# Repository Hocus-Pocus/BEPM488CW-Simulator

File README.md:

# BEPM488CW-Simulator
Simulator hardware for the BEPM488CW project

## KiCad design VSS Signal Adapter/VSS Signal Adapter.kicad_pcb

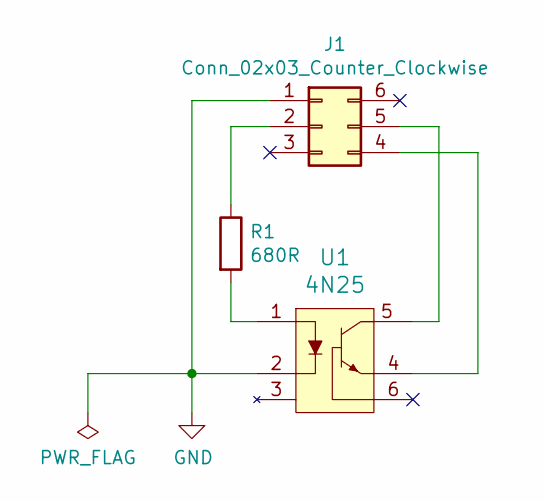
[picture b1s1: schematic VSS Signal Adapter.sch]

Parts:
J1: Conn_02x03_Counter_Clockwise; DIP-6_W7.62mm
R1: 680R; R_Axial_DIN0207_L6.3mm_D2.5mm_P10.16mm_Horizontal
U1: 4N25; DIP-6_W7.62mm; MPN 4N25; Digi-Key_PN 160-1300-5-ND

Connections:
GND: J1.1, U1.2
unnamed: J1.2, R1.1
unnamed: J1.4, U1.4
unnamed: J1.5, U1.5
unnamed: R1.2, U1.1

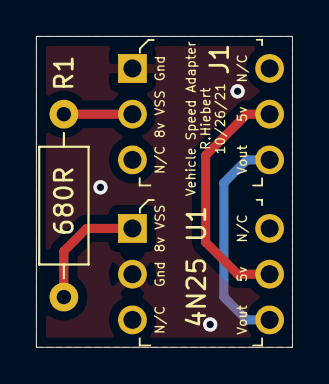
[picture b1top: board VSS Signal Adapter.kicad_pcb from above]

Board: 2 copper layers, 14.2 x 17.3 mm, 3 parts (0 on the bottom side), 5 nets.

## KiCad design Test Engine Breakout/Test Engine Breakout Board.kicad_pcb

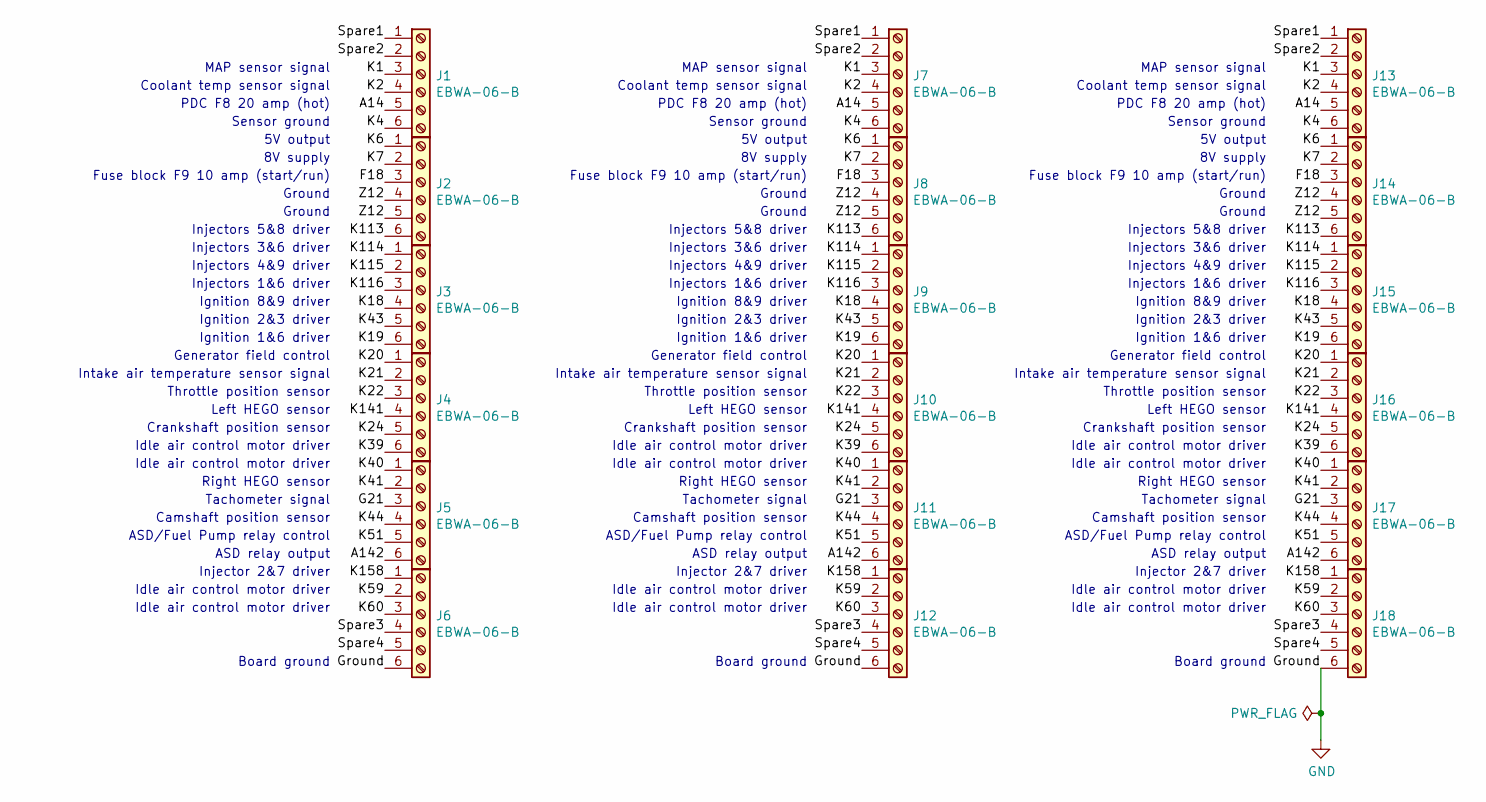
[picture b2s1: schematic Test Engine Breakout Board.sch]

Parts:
J1, J2, J3, J4, J5, J6, J7, J8, J9, J10, J11, J12, J13, J14, J15, J16, J17, J18: EBWA-06-B

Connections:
/A14: J1.5, J7.5, J13.5
/A142: J5.6, J11.6, J17.6
/F18: J2.3, J8.3, J14.3
/G21: J5.3, J11.3, J17.3
/K1: J1.3, J7.3, J13.3
/K2: J1.4, J7.4, J13.4
/K4: J1.6, J7.6, J13.6
/K6: J2.1, J8.1, J14.1
/K7: J2.2, J8.2, J14.2
/K18: J3.4, J9.4, J15.4
/K19: J3.6, J9.6, J15.6
/K20: J4.1, J10.1, J16.1
/K21: J4.2, J10.2, J16.2
/K22: J4.3, J10.3, J16.3
/K24: J4.5, J10.5, J16.5
/K39: J4.6, J10.6, J16.6
/K40: J5.1, J11.1, J17.1
/K41: J5.2, J11.2, J17.2
/K43: J3.5, J9.5, J15.5
/K44: J5.4, J11.4, J17.4
/K51: J5.5, J11.5, J17.5
/K59: J6.2, J12.2, J18.2
/K60: J6.3, J12.3, J18.3
/K113: J2.6, J8.6, J14.6
/K114: J3.1, J9.1, J15.1
/K115: J3.2, J9.2, J15.2
/K116: J3.3, J9.3, J15.3
/K141: J4.4, J10.4, J16.4
/K158: J6.1, J12.1, J18.1
/Spare1: J1.1, J7.1, J13.1
/Spare2: J1.2, J7.2, J13.2
/Spare3: J6.4, J12.4, J18.4
/Spare4: J6.5, J12.5, J18.5
/Z12: J2.4, J2.5, J8.4, J8.5, J14.4, J14.5
GND: J6.6, J12.6, J18.6

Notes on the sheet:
MAP sensor signal
Coolant temp sensor signal
PDC F8 20 amp (hot)
Sensor ground
5V output
8V supply
Fuse block F9 10 amp (start/run)
Ground
Injectors 5&8 driver
Injectors 3&6 driver
Injectors 4&9 driver
Injectors 1&6 driver
Ignition 8&9 driver
Ignition 2&3 driver
Ignition 1&6 driver
Generator field control
Intake air temperature sensor signal
Throttle position sensor
Left HEGO sensor
Crankshaft position sensor
Idle air control motor driver
Right HEGO sensor
Tachometer signal
Camshaft position sensor
ASD/Fuel Pump relay control
ASD relay output
Injector 2&7 driver
Board ground

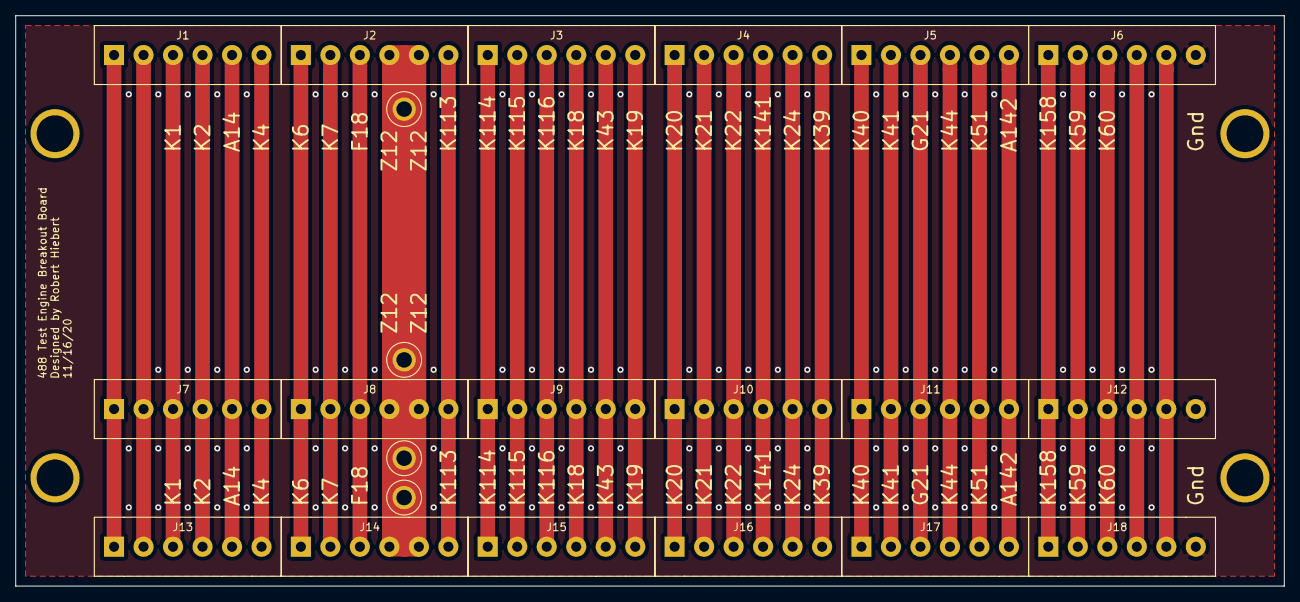
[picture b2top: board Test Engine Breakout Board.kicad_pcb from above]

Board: 2 copper layers, 163.8 x 73.7 mm, 18 parts (0 on the bottom side), 35 nets.

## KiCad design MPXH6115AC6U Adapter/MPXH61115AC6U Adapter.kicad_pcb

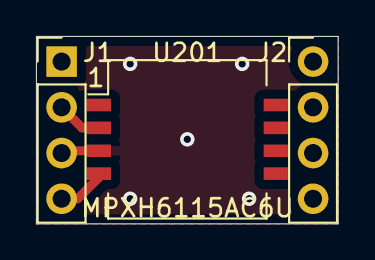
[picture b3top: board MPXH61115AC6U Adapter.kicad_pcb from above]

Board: 2 copper layers, 16.8 x 10.4 mm, 3 parts (0 on the bottom side), 3 nets.

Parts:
J1: Conn_01x04-1to4; PinHeader_1x04_P2.54mm_Vertical_1to4
J2: Conn_01x04_5to8; PinHeader_1x04_P2.54mm_Vertical_5to8
U201: MPXH6115AC6U; Freescale_98ARH99089A

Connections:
+5V: J1.2, U201.2
GND: J1.3, U201.3
unnamed: J1.4, U201.4

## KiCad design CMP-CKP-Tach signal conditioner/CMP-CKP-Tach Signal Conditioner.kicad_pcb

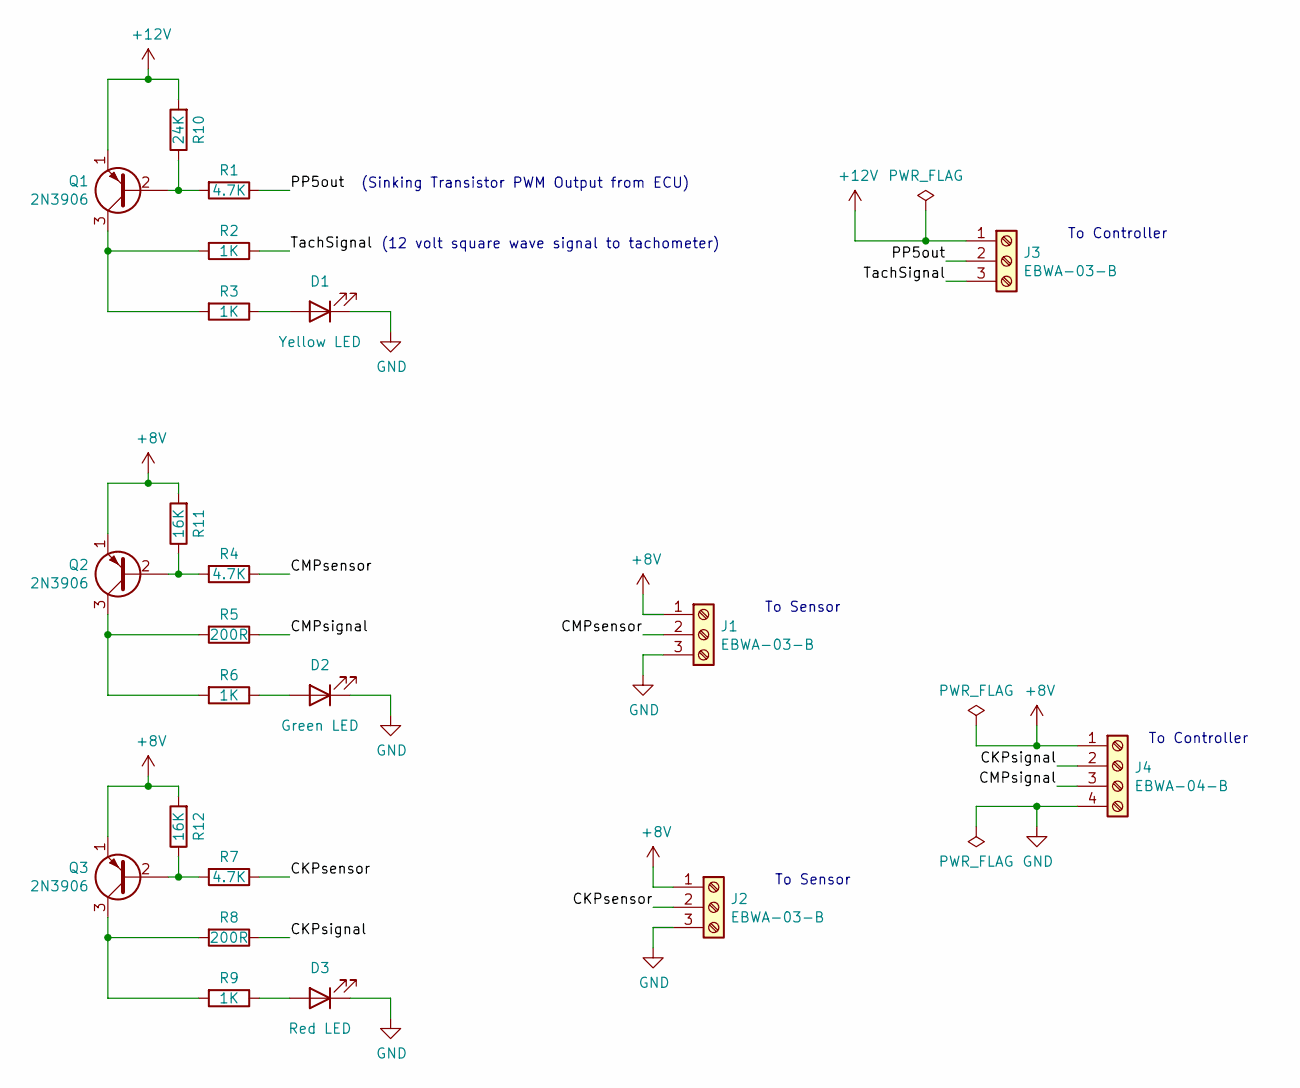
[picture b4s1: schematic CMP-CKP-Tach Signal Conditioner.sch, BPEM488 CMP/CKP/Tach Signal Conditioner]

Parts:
D1: Yellow LED; LED_D3.0mm; Digikey PN VA0L-3MDE2-ND
D2: Green LED; LED_D3.0mm; Digikey PN VA0L-3MDE2-ND
D3: Red LED; LED_D3.0mm
J1: EBWA-03-B; Digikey PN 2057-EBWA-03-B-ND
J2, J3: EBWA-03-B
J4: EBWA-04-B; Digikey PN 2057-EBWA-04-B-ND
Q1, Q2, Q3: 2N3906; TO-92_Wide
R1, R4, R7: 4.7K; R_Axial_DIN0207_L6.3mm_D2.5mm_P7.62mm_Horizontal
R2, R3, R6, R9: 1K; R_Axial_DIN0207_L6.3mm_D2.5mm_P7.62mm_Horizontal
R5, R8: 200R; R_Axial_DIN0207_L6.3mm_D2.5mm_P7.62mm_Horizontal
R10: 24K; R_Axial_DIN0207_L6.3mm_D2.5mm_P7.62mm_Horizontal
R11, R12: 16K; R_Axial_DIN0207_L6.3mm_D2.5mm_P7.62mm_Horizontal

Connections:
+8V: J1.1, J2.1, J4.1, Q2.1 (E), Q3.1 (E), R11.2, R12.2
+12V: J3.1, Q1.1 (E), R10.2
/CKPsensor: J2.2, R7.1
/CKPsignal: J4.2, R8.1
/CMPsensor: J1.2, R4.1
/CMPsignal: J4.3, R5.1
/PP5out: J3.2, R1.1
/TachSignal: J3.3, R2.1
GND: D1.1 (K), D2.1 (K), D3.1 (K), J1.3, J2.3, J4.4
unnamed: D1.2 (A), R3.1
unnamed: D2.2 (A), R6.1
unnamed: D3.2 (A), R9.1
unnamed: Q1.2 (B), R1.2, R10.1
unnamed: Q1.3 (C), R2.2, R3.2
unnamed: Q2.2 (B), R4.2, R11.1
unnamed: Q2.3 (C), R5.2, R6.2
unnamed: Q3.2 (B), R7.2, R12.1
unnamed: Q3.3 (C), R8.2, R9.2

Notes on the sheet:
(Sinking Transistor PWM Output from ECU)
(12 volt square wave signal to tachometer)
To Sensor
To Controller

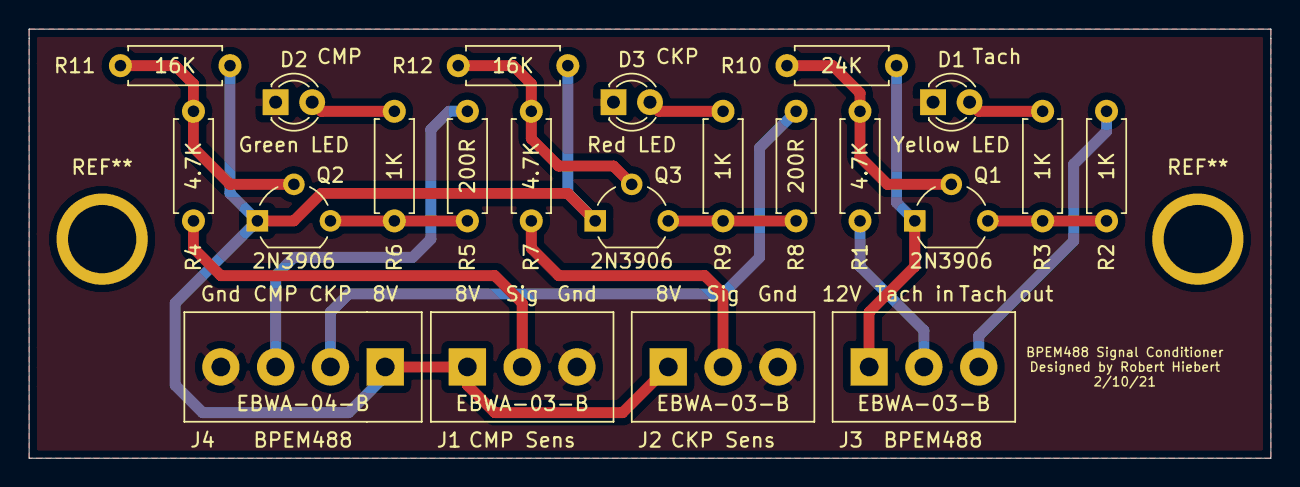
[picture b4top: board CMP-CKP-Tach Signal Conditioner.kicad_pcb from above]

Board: 2 copper layers, 86.4 x 29.8 mm, 22 parts (0 on the bottom side), 18 nets.

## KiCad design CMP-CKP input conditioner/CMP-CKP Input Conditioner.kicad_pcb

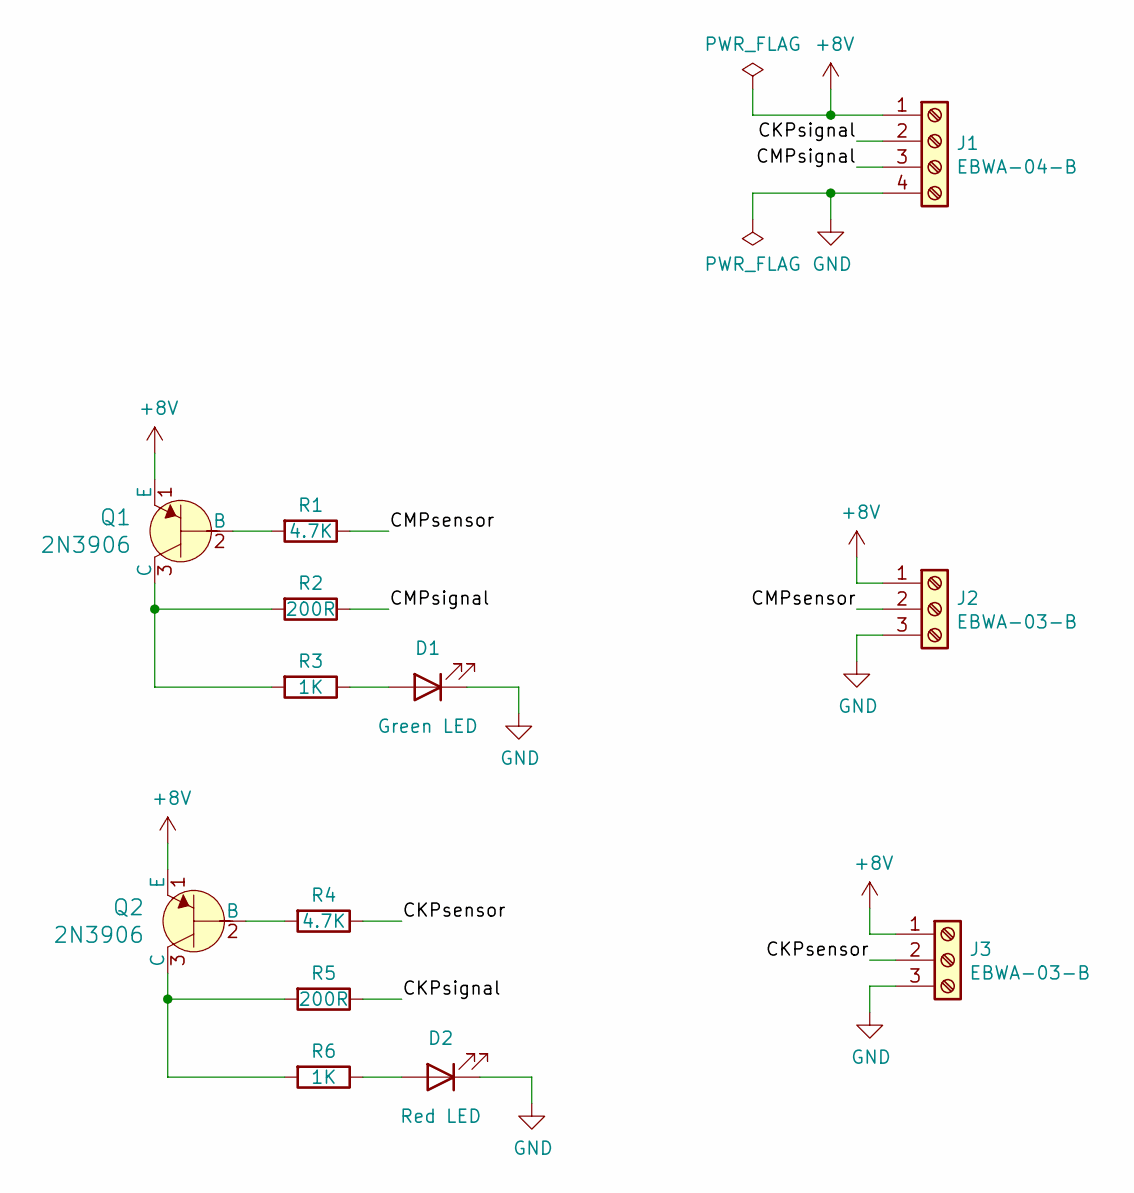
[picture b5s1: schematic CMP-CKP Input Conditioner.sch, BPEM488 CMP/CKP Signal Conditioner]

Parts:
D1: Green LED; LED_D3.0mm; Digikey PN VA0L-3MDE2-ND
D2: Red LED; LED_D3.0mm
J1: EBWA-04-B; Digikey PN 2057-EBWA-04-B-ND
J2: EBWA-03-B; Digikey PN 2057-EBWA-03-B-ND
J3: EBWA-03-B
Q1, Q2: 2N3906; TO-92_Wide; MPN 2N3906; Digi-Key_PN 2N3906APCT-ND
R1, R4: 4.7K; R_Axial_DIN0207_L6.3mm_D2.5mm_P7.62mm_Horizontal
R2, R5: 200R; R_Axial_DIN0207_L6.3mm_D2.5mm_P7.62mm_Horizontal
R3, R6: 1K; R_Axial_DIN0207_L6.3mm_D2.5mm_P7.62mm_Horizontal

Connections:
+8V: J1.1, J2.1, J3.1, Q1.1 (E), Q2.1 (E)
/CKPsensor: J3.2, R4.1
/CKPsignal: J1.2, R5.1
/CMPsensor: J2.2, R1.1
/CMPsignal: J1.3, R2.1
GND: D1.1 (K), D2.1 (K), J1.4, J2.3, J3.3
unnamed: D1.2 (A), R3.1
unnamed: D2.2 (A), R6.1
unnamed: Q1.2 (B), R1.2
unnamed: Q1.3 (C), R2.2, R3.2
unnamed: Q2.2 (B), R4.2
unnamed: Q2.3 (C), R5.2, R6.2

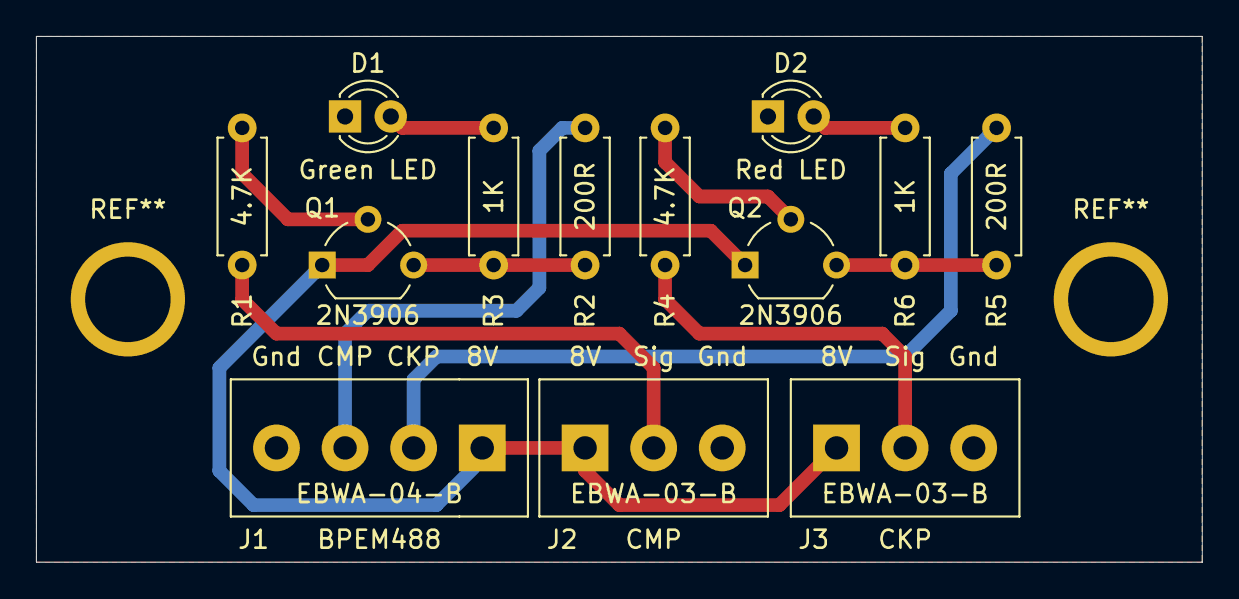
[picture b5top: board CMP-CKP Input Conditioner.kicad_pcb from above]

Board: 2 copper layers, 64.8 x 29.2 mm, 13 parts (0 on the bottom side), 12 nets.

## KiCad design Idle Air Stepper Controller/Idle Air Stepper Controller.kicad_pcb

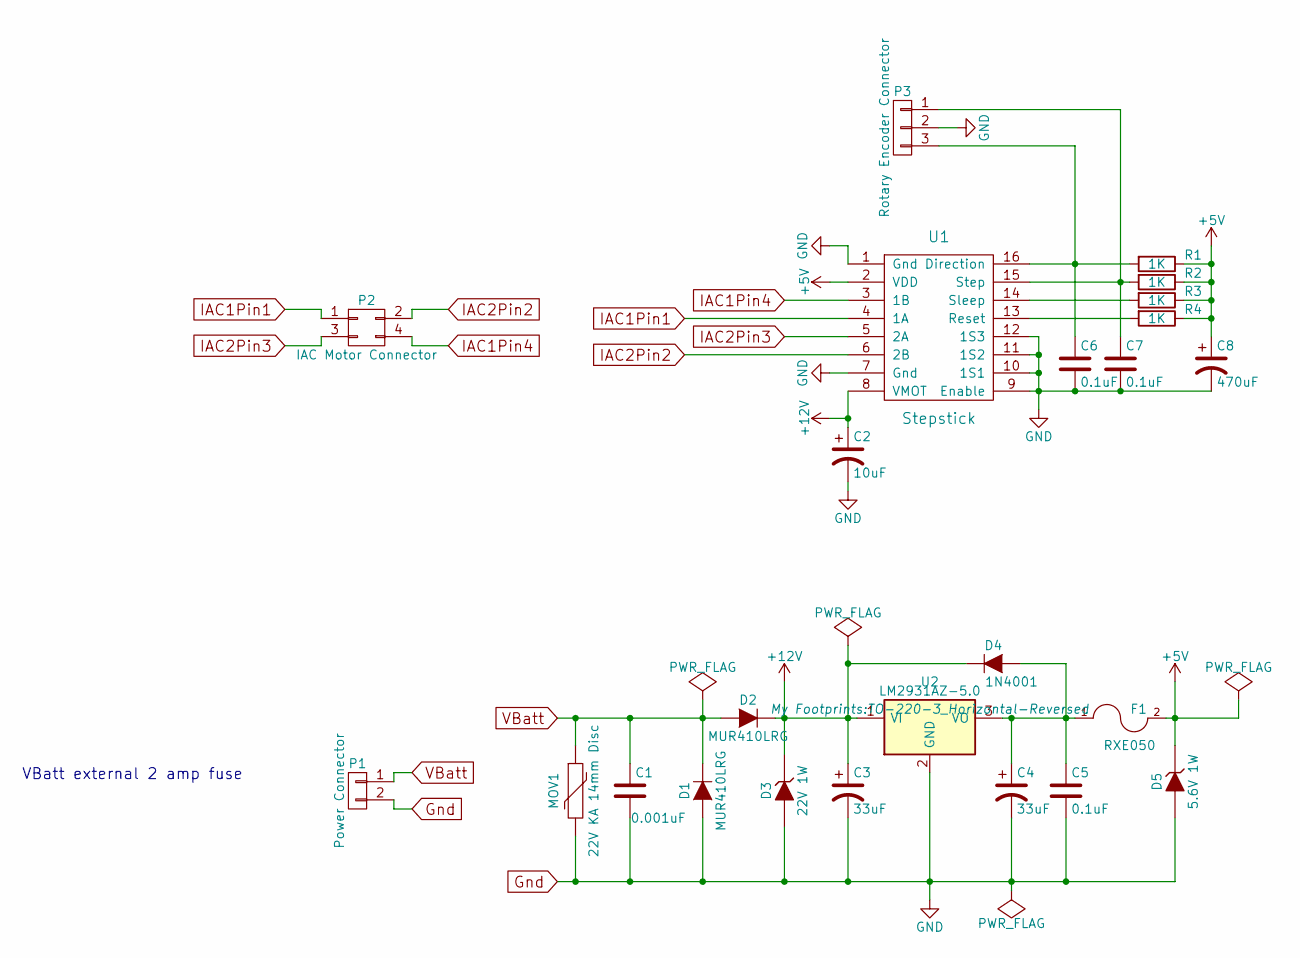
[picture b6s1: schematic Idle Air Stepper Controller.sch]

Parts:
C1: 0.001uF; 1000pF
C2: 10uF
C3, C4: 33uF
C5, C6, C7: 0.1uF
C8: 470uF
D1, D2: MUR410LRG; MUR410RLG
D3: 22V 1W; SmallZener
D4: 1N4001; 1N4001G
D5: 5.6V 1W; SmallZener
F1: RXE050; RXEF050
MOV1: 22V KA 14mm Disc; 14mmVar
P1: Power Connector; Molex-Microfit3-Single2-90
P2: IAC Motor Connector; Molex-Microfit3-Dual4-90
P3: Rotary Encoder Connector; Molex-Microfit3-Single3-90
R1, R2, R3, R4: 1K; .25Wresistor
U1: Stepstick
U2: LM2931AZ-5.0; TO-220-3_Horizontal-Reversed

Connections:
+5V: C8.1, D5.1 (K), F1.2, R1.1, R2.1, R3.1, R4.1, U1.2 (VDD)
+12V: C2.1, C3.1, D2.1 (K), D3.1 (K), D4.1 (K), U1.8 (VMOT), U2.1 (VI)
Gnd: C1.2, C2.2, C3.2, C4.2, C5.2, C6.2, C7.2, C8.2, D1.2 (A), D3.2 (A), D5.2 (A), MOV1.2, P1.2, P3.2, U1.1 (Gnd), U1.7 (Gnd), U1.9 (Enable), U1.10 (1S1), U1.11 (1S2), U1.12 (1S3), U2.2 (GND)
IAC1Pin1: P2.1, U1.4 (1A)
IAC1Pin4: P2.4, U1.3 (1B)
IAC2Pin2: P2.2, U1.6 (2B)
IAC2Pin3: P2.3, U1.5 (2A)
unnamed: C4.1, C5.1, D4.2 (A), F1.1, U2.3 (VO)
unnamed: C6.1, P3.3, R1.2, U1.16 (Direction)
unnamed: C7.1, P3.1, R2.2, U1.15 (Step)
unnamed: R3.2, U1.14 (Sleep)
unnamed: R4.2, U1.13 (Reset)
VBatt: C1.1, D1.1 (K), D2.2 (A), MOV1.1, P1.1

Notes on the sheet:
VBatt external 2 amp fuse

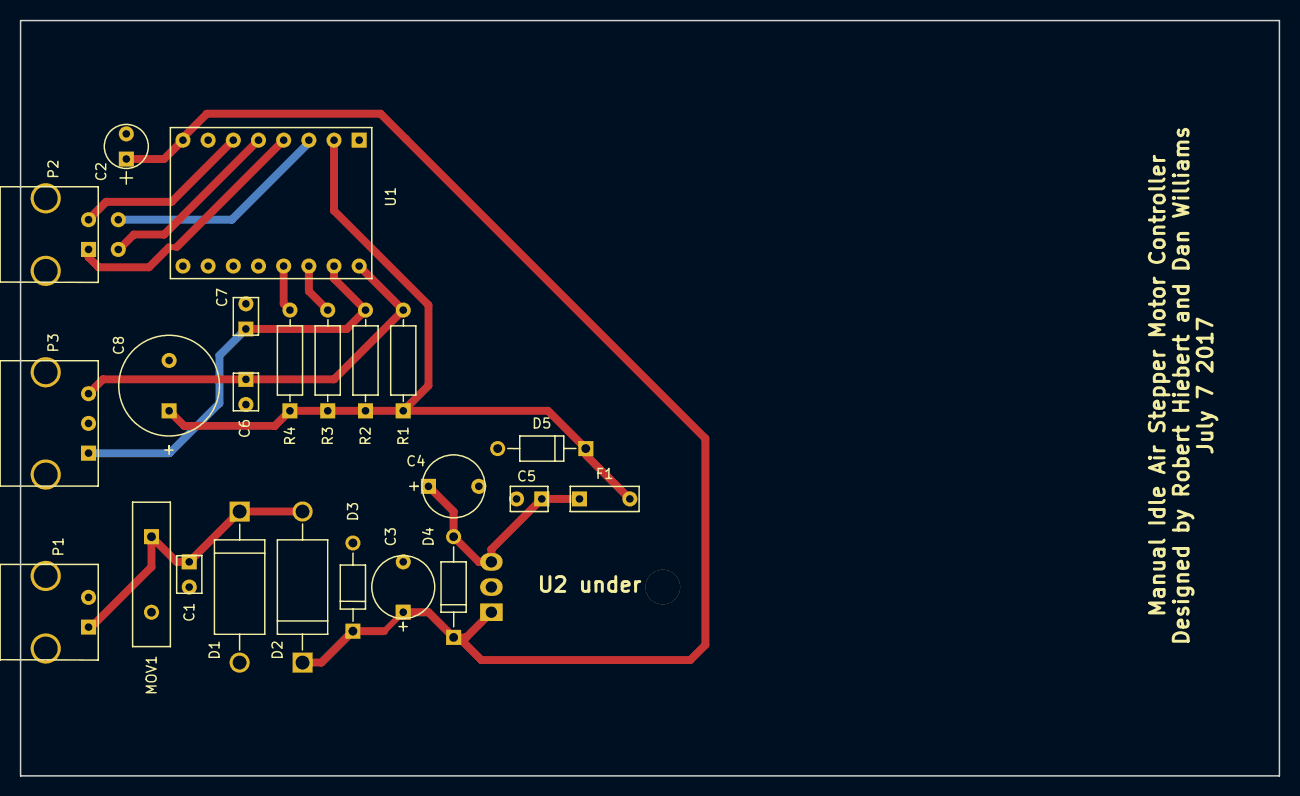
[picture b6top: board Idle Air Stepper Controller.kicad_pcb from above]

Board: 2 copper layers, 127.0 x 76.2 mm, 24 parts (1 on the bottom side), 13 nets.

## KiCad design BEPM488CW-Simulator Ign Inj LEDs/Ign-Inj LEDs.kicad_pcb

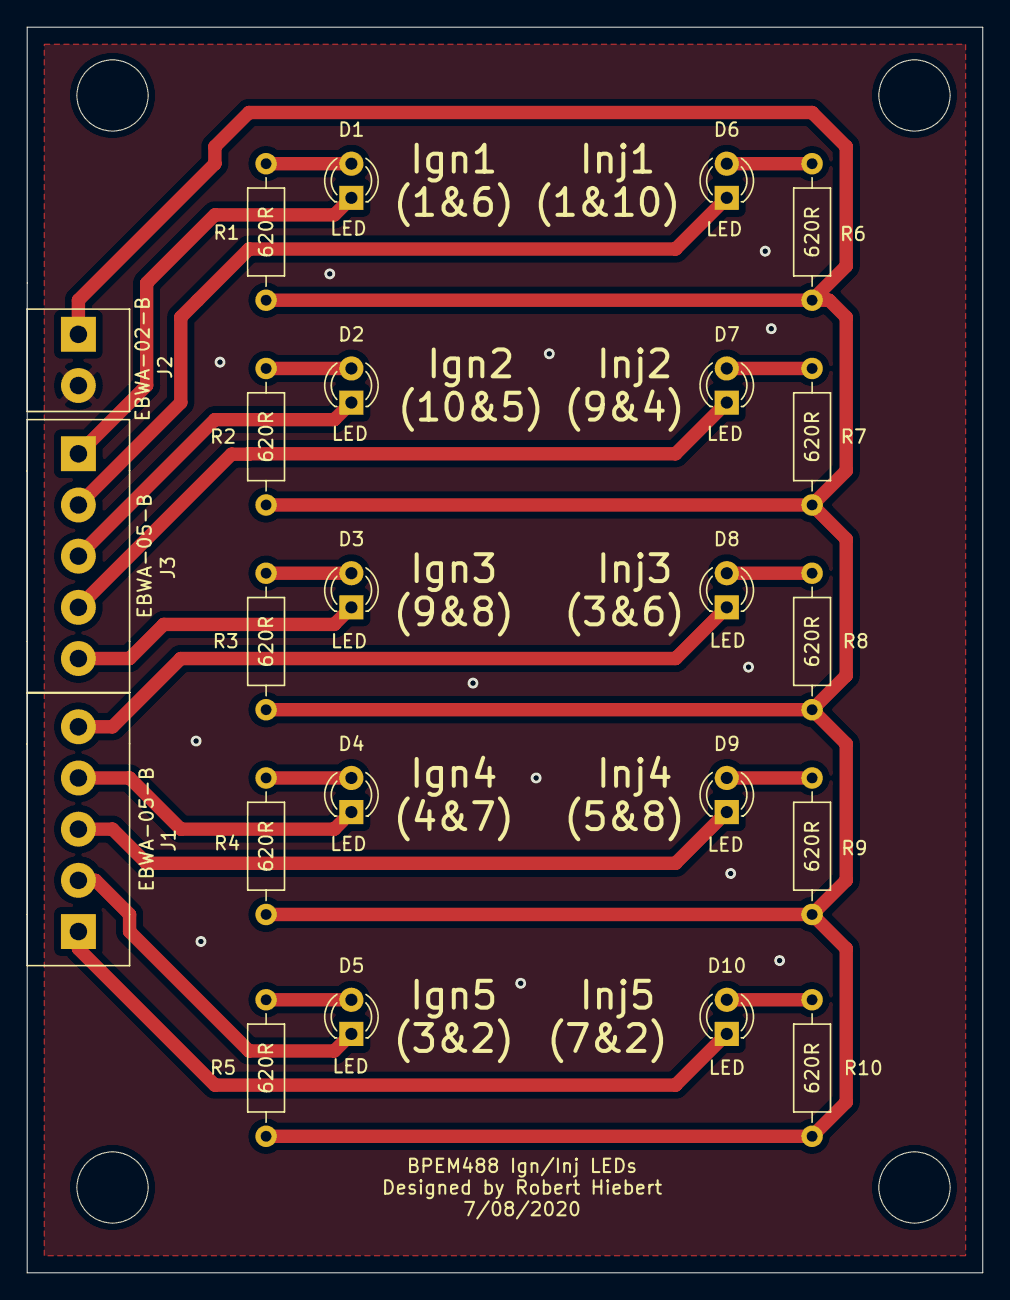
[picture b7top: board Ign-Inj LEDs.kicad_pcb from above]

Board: 2 copper layers, 71.1 x 92.7 mm, 23 parts (0 on the bottom side), 21 nets.

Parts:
D1, D2, D3, D4, D5, D6, D7, D8, D9, D10: LED; LED_D3.0mm
J1, J3: EBWA-05-B
J2: EBWA-02-B
R1, R2, R3, R4, R5, R6, R7, R8, R9, R10: 620R; R_Axial_DIN0207_L6.3mm_D2.5mm_P10.16mm_Horizontal

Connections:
+12V: J2.1, R1.1, R2.1, R3.1, R4.1, R5.1, R6.2, R7.2, R8.2, R9.2, R10.2
/Inj1: D6.1, J3.2
/Inj2: D7.1, J3.4
/Inj3: D8.1, J1.5
/Inj4: D9.1, J1.3
/Inj5: D10.1, J1.1
unnamed: D1.1, J3.1
unnamed: D1.2, R1.2
unnamed: D2.1, J3.3
unnamed: D2.2, R2.2
unnamed: D3.1, J3.5
unnamed: D3.2, R3.2
unnamed: D4.1, J1.4
unnamed: D4.2, R4.2
unnamed: D5.1, J1.2
unnamed: D5.2, R5.2
unnamed: D6.2, R6.1
unnamed: D7.2, R7.1
unnamed: D8.2, R8.1
unnamed: D9.2, R9.1
unnamed: D10.2, R10.1

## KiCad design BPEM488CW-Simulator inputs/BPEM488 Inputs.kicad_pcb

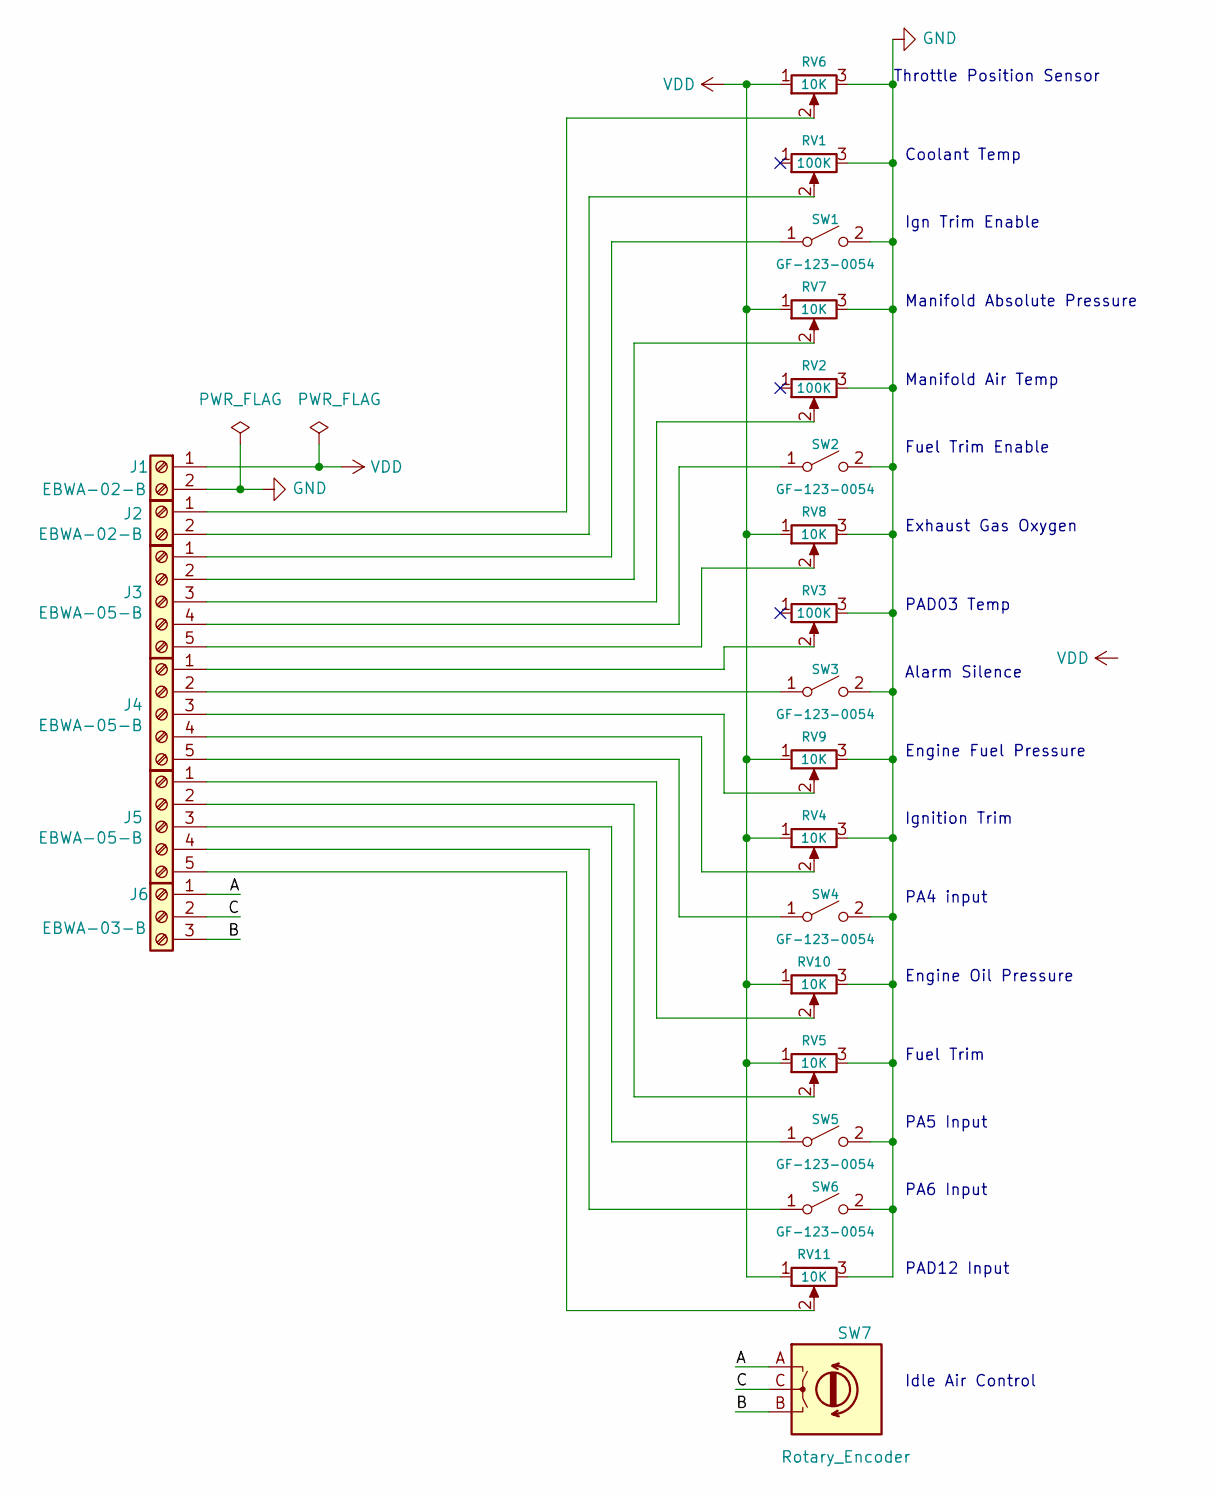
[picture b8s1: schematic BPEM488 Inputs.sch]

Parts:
J1, J2: EBWA-02-B; Digikey 2057-EBWA-02-B-ND
J3, J4, J5: EBWA-05-B; Digikey 2057-EBWA-05-B-ND
J6: EBWA-03-B; Digikey 2057-EBWA-03-B-ND
RV1, RV2, RV3: 100K; 23ESA104mmF50NF; Digikey A105767-ND
RV4, RV5, RV6, RV7, RV8, RV9, RV10, RV11: 10K; PDB241-E420K-103B0; Digikey PDB241-E420K-103B0-ND
SW1, SW2, SW3, SW4, SW5, SW6: GF-123-0054; Digikey CW1333-ND
SW7: Rotary_Encoder; Rotary Encoder

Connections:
/A: J6.1, SW7.A
/B: J6.3, SW7.B
/C: J6.2, SW7.C
GND: J1.2, RV1.3, RV2.3, RV3.3, RV4.3, RV5.3, RV6.3, RV7.3, RV8.3, RV9.3, RV10.3, RV11.3, SW1.2 (B), SW2.2 (B), SW3.2 (B), SW4.2 (B), SW5.2 (B), SW6.2 (B)
unnamed: J2.1, RV6.2
unnamed: J2.2, RV1.2
unnamed: J3.1, SW1.1 (A)
unnamed: J3.2, RV7.2
unnamed: J3.3, RV2.2
unnamed: J3.4, SW2.1 (A)
unnamed: J3.5, RV8.2
unnamed: J4.1, RV3.2
unnamed: J4.2, SW3.1 (A)
unnamed: J4.3, RV9.2
unnamed: J4.4, RV4.2
unnamed: J4.5, SW4.1 (A)
unnamed: J5.1, RV10.2
unnamed: J5.2, RV5.2
unnamed: J5.3, SW5.1 (A)
unnamed: J5.4, SW6.1 (A)
unnamed: J5.5, RV11.2
VDD: J1.1, RV4.1, RV5.1, RV6.1, RV7.1, RV8.1, RV9.1, RV10.1, RV11.1

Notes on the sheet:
Ign Trim Enable
Fuel Trim Enable
Alarm Silence
PA4 input
PA5 Input
PA6 Input
Coolant Temp
Manifold Air Temp
PAD03 Temp
Ignition Trim
Fuel Trim
Throttle Position Sensor
Manifold Absolute Pressure
Exhaust Gas Oxygen
Engine Fuel Pressure
Engine Oil Pressure
PAD12 Input
Idle Air Control

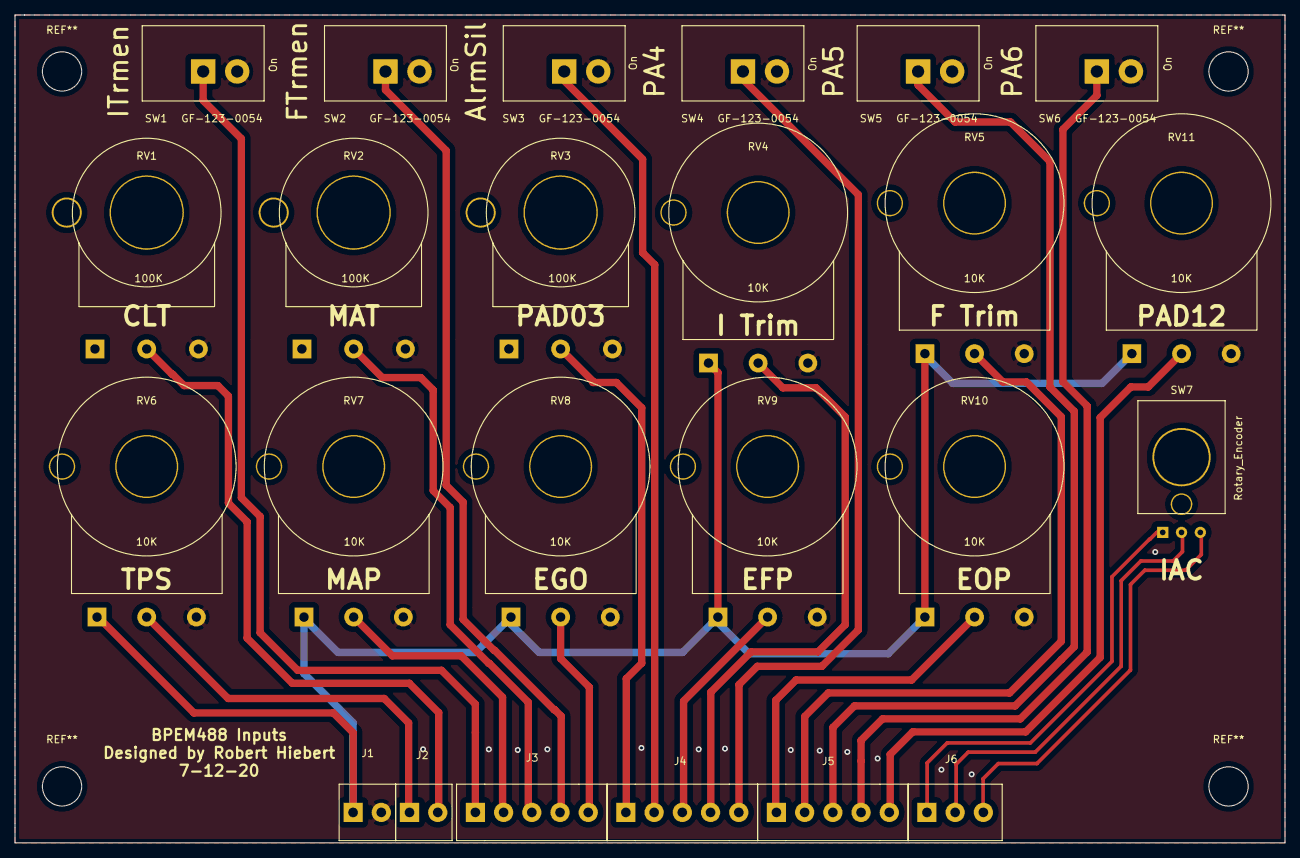
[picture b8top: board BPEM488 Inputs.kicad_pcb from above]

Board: 2 copper layers, 171.4 x 111.8 mm, 24 parts (0 on the bottom side), 22 nets.

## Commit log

2022-11-15 Create Git Hold
